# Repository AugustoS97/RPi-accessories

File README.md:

# RPi-accessories

Repositorio con diferentes PCBs de uso con Arduino y Rapsberry

## Contenido del repositorio

- [PCB para control PWM](/PWM-TRANSISTOR-PCB/) de elementos de tensión igual o superior a la de alimentación del microcontrolador. Compatible con Arduino, Raspberry, ESP, etc.

- [PCB de expansión para Rapsberry](/LED-RPi-PCB/). Permite alimentar RPi desde fuente externa, conectar un elementos para control PWM (ventilador por ejemplo), LEDs de estado, fusible de protección y pines de expansión para alimentación.

## Como ordenar las PCB

- Cada subproyecto dispone de una carpeta GERBER para ser subida a JLCPCB o PCBWAY y poder pedir las placas. Puedes adquirirse individualmente y soldadas contactando conmigo vía email: augustosamuelhdezmartin@gmail.com
- Existe una carpeta con GERBER para el panelizado de las PCB para ahorrar costes en JLCPCB.

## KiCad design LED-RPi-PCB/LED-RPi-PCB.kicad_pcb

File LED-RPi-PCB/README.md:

# PWM-RPi-PCB

Módulo de expansión para Rapsberry Pi. Permite alimentar RPi desde una fuente externa superior a 5V, incorpora un módulo para control PWM de una salida, LEDs indicadores de Estado y de Alimentación, Fusible de Protección, y pines de expansión para aumentar las conexiones de 3.3V y 5V. Diseñado para ser utilizado en el [NAS expuesto aquí](https://github.com/AugustoS97/Raspberry-Pi-NAS).

## Características

- Permite alimentar RPi desde una fuente externa superior a 5V con módulos LM2596 y MP2307
- Incorpora un módulo para control PWM de una salida de hasta 625mW
- LEDs indicadores de Estado y de Alimentación
- Fusible de Protección 5x20
- Pines de expansión para aumentar las conexiones de 3.3V y 5V
- Cuenta con Jumper (JP2) para desactivar o activar los LEDs indicadores
- Incorpora un Jumper/Pines (JP1) para conectar un interruptor de encendido y apagado del módulo mediante conectores Dupont
- Dimensiones 58,7mm x 43,9mm
- GERBER disponibles para solicitar las PCB. Si desea comprarlas ensambladas por unidades, puedes contactarme a augustosamuelhdezmartin@gmail.com

## Características de la salida PWM 

- Corriente máxima: 600mA
- Potencia máxima: 625mW
- Pensado para controlar motores desde Raspberry y Arduino (3,3V y 5V de señal de control). Puede modificarse R1 y R2 para ser utilizado con otras tensiones de control.

## Lista de materiales (BOM)

- Transistor 2N2222A SOT-23
- Resistencia 1206 1K 0.25W x2 unidades
- Resistencia 1206 10K 0.25W
- Resistencia 1206 220Ohm 
- Módulo DC/DC MP2307 o LM2596
- Diodo 1N4007 SOD-123F
- PinHeader 2.54mm 9 pines x2 unidades
- Portafuisble 5x20
- Jumpers x2 unidades
- LED 5mm x2 unidades (rojo y verde)
- PinHeader 2.54mm 2 pines x3 unidades
- Conector DC-Jack

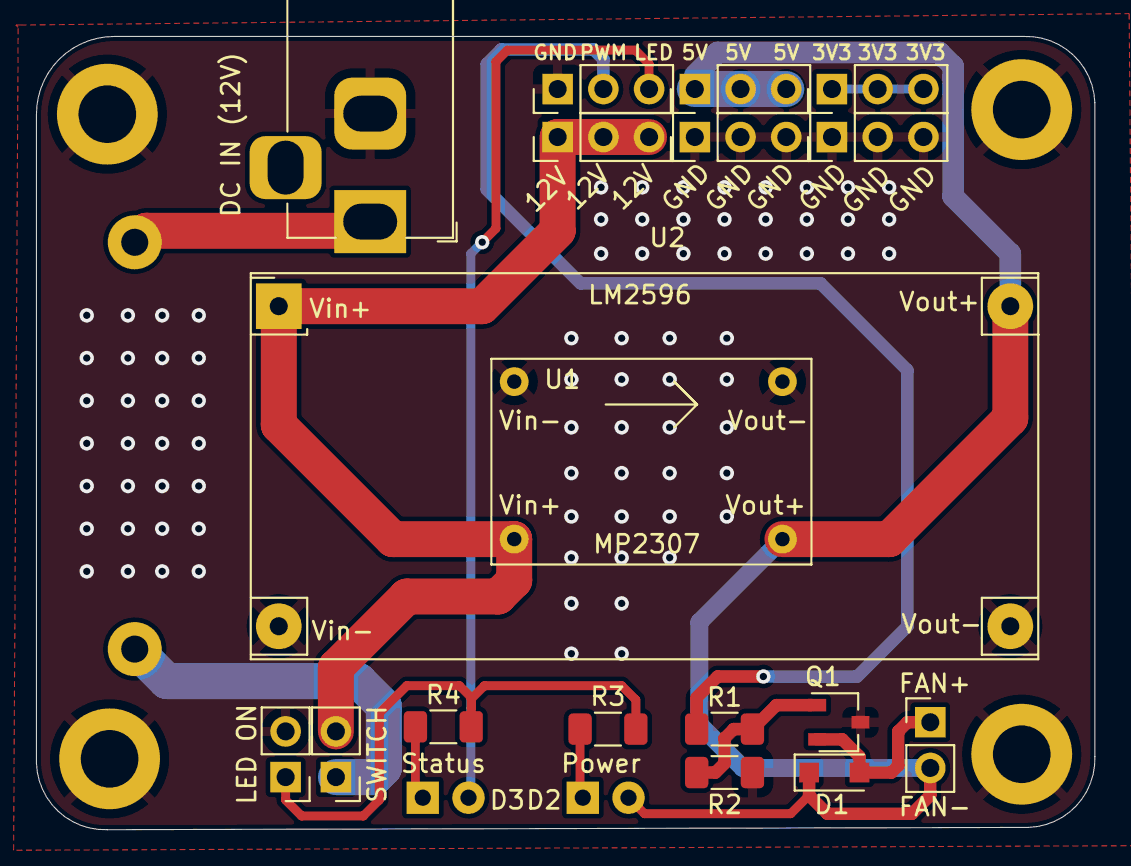
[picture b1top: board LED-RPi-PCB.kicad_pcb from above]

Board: 2 copper layers, 58.8 x 44.1 mm, 25 parts (0 on the bottom side), 13 nets.

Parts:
D1: 1N4007; D_SOD-123F
D2: RED; LED_D3.0mm_Horizontal_O1.27mm_Z2.0mm
D3: YELLOW; LED_D3.0mm_Horizontal_O1.27mm_Z2.0mm
F1: 1,5A; Fuseholder_Cylinder-5x20mm_Stelvio-Kontek_PTF78_Horizontal_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
H1, H2, H3, H4: MountingHole_Pad; MountingHole_3.2mm_M3_DIN965_Pad
J1: FAN_CON; PinHeader_1x02_P2.54mm_Vertical
J2: RPi_IN; PinHeader_1x03_P2.54mm_Vertical
J3, J8: GND_CON; PinHeader_1x03_P2.54mm_Vertical
J4: 12V_CON; PinHeader_1x03_P2.54mm_Vertical
J5: 5V_CON; PinHeader_1x03_P2.54mm_Vertical
J6: 3V3_CON; PinHeader_1x03_P2.54mm_Vertical
J7: Jack-DC; BarrelJack_Horizontal
JP1: Jumper & Switch; PinHeader_1x02_P2.54mm_Vertical
JP2: LED_ON; PinHeader_1x02_P2.54mm_Vertical
Q1: 2N2222A; SOT-23W
R1, R3: 1k; R_1206_3216Metric_Pad1.30x1.75mm_HandSolder
R2: 10k; R_1206_3216Metric_Pad1.30x1.75mm_HandSolder
R4: 220; R_1206_3216Metric_Pad1.30x1.75mm_HandSolder
U1: MP2307
U2: DCDC_StepDown_LM2596

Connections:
+3V3: J6.1, J6.2, J6.3
+5V: D1.1, D2.2, J1.2, J5.1, J5.2, J5.3, U1.3, U2.4
+12V: J4.1, J4.2, J4.3, JP1.2, U1.1, U2.1
/FAN_V-: D1.2, J1.1, Q1.2
GND: H1.1, H2.1, H3.1, H4.1, J2.1, J3.1, J3.2, J3.3, J7.2, J8.1, J8.2, J8.3, JP2.2, Q1.3, R2.2, U1.2, U1.4, U2.2, U2.3
unnamed: D2.1, R3.1
unnamed: D3.1, R4.1
unnamed: F1.1, JP1.1
unnamed: JP2.1, R3.2, R4.2
unnamed: Q1.1, R1.1, R2.1
PWM: J2.2, R1.2
StatusLED+: D3.2, J2.3
VDC: F1.2, J7.1

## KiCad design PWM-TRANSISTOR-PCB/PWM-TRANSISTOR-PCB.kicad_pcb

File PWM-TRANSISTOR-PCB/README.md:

# PWM-TRANSISTOR-PCB

Módulo para el control PWM de cualquier elemento que trabaje con tensión igual o superior a la de alimentación.

- Corriente máxima: 600mA
- Potencia máxima: 625mW
- Pensado para controlar motores desde Raspberry y Arduino (3,3V y 5V de señal de control). Puede modificarse R1 y R2 para ser utilizado con otras tensiones de control.
- GERBER disponibles para solicitar las PCB. Si desea comprarlas ensambladas por unidades, puedes contactarme a augustosamuelhdezmartin@gmail.com
- Dimensiones de la PCB 26,7mm x 23,9 mm.

## Lista de materiales (BOM)

- Transistor 2N2222A SOT-23
- Resistencia 1206 1K 0.25W
- Resistencia 1206 10K 0.25W
- Diodo 1N4007 SOD-123F
- PinHeader 2.54 2 pines x3 unidades
- Terminal Block 5.08mm

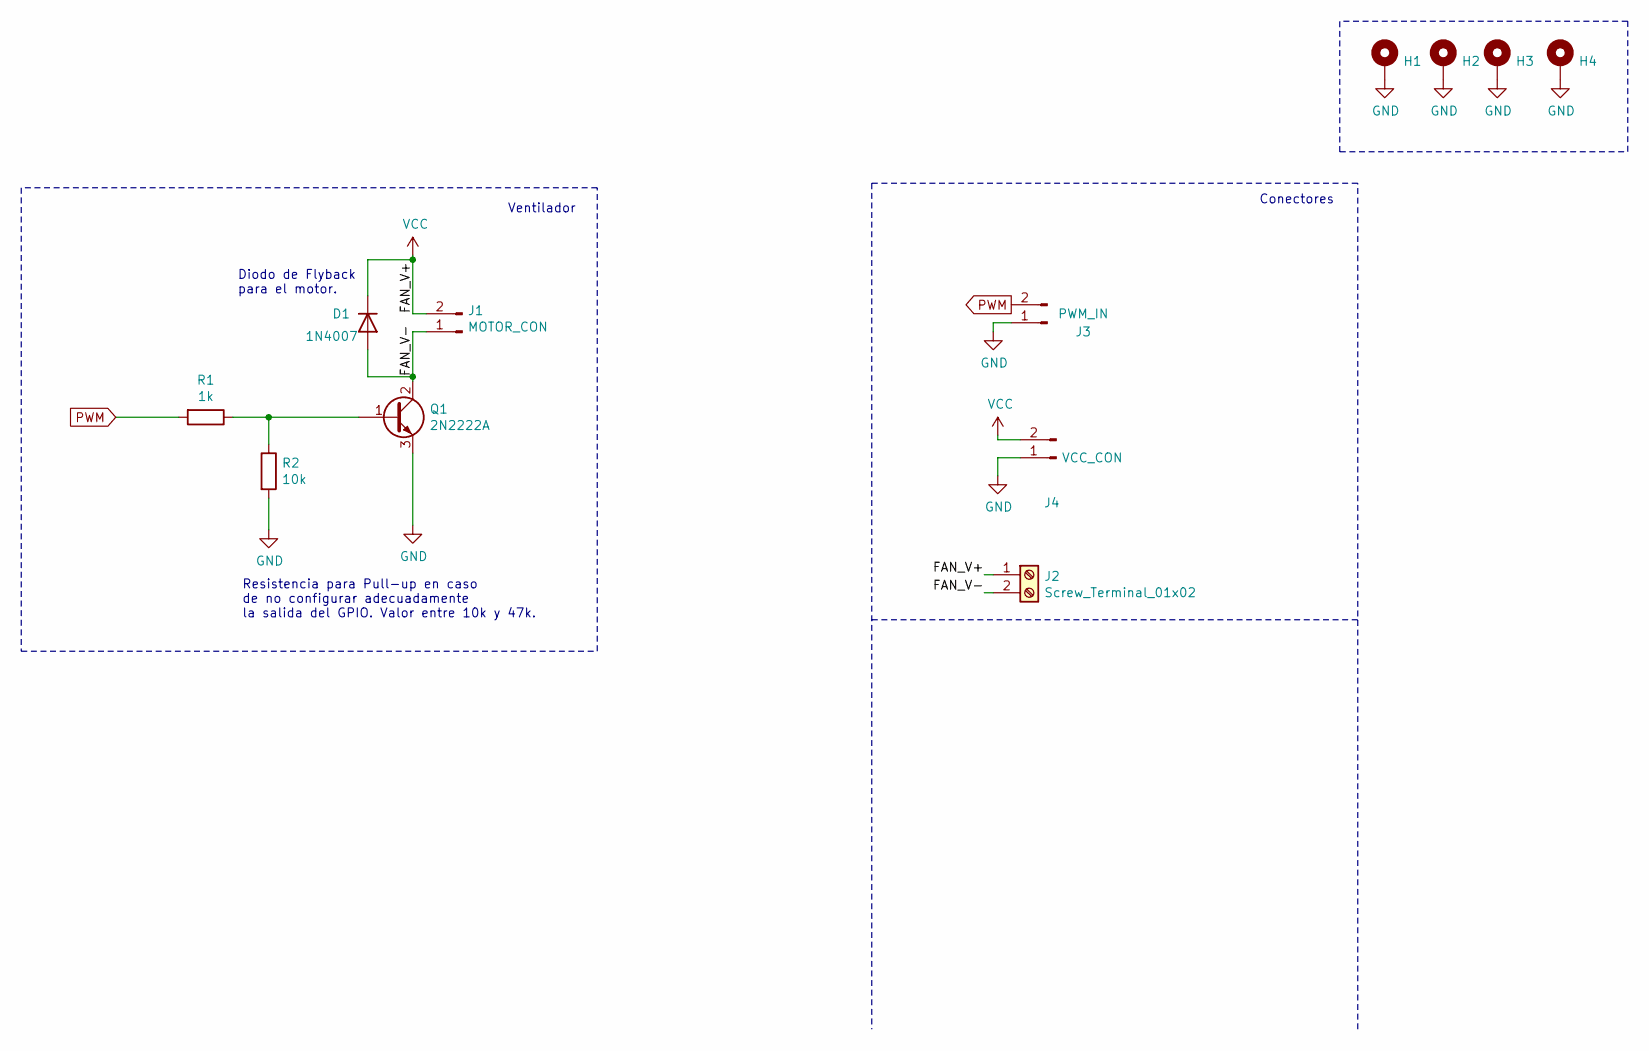
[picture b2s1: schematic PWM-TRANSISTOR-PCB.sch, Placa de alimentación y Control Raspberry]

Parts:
D1: 1N4007; D_SOD-123F
H1, H2, H3, H4: MountingHole_Pad; MountingHole_3.2mm_M3_DIN965_Pad
J1: MOTOR_CON; PinHeader_1x02_P2.54mm_Vertical
J2: Screw_Terminal_01x02; TerminalBlock_bornier-2_P5.08mm
J3: PWM_IN; PinHeader_1x02_P2.54mm_Vertical
J4: VCC_CON; PinHeader_1x02_P2.54mm_Vertical
Q1: 2N2222A; SOT-23_Handsoldering
R1: 1k; R_1206_3216Metric_Pad1.30x1.75mm_HandSolder
R2: 10k; R_1206_3216Metric_Pad1.30x1.75mm_HandSolder

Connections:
/FAN_V-: D1.2 (A), J1.1, J2.2, Q1.2 (C)
GND: H1.1, H2.1, H3.1, H4.1, J3.1, J4.1, Q1.3 (E), R2.2
unnamed: Q1.1 (B), R1.1, R2.1
PWM: J3.2, R1.2
VCC: D1.1 (K), J1.2, J2.1, J4.2

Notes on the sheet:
Resistencia para Pull-up en caso de no configurar adecuadamente la salida del GPIO. Valor entre 10k y 47k.
Diodo de Flyback para el motor.
Conectores
Ventilador

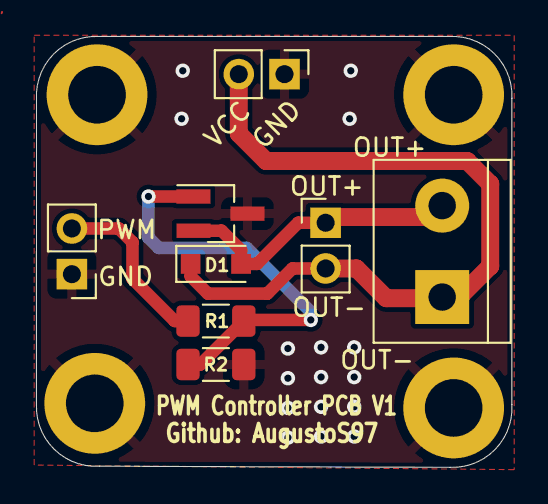
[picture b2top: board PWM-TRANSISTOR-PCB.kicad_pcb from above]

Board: 2 copper layers, 26.4 x 23.9 mm, 12 parts (0 on the bottom side), 5 nets.

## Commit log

2022-06-15 Creada la version V1.0 de la PCB para DCDC, ventilador y LEDs
2022-07-15 Creada PCB para controlar motores con PWM y Transistor. Añadidos logos DCD
2022-08-14 Añadidos las README así como GERBERS y RENDERs
2022-08-14 Eliminados ficheros extra
2022-11-14 Añadido STEP de PCB
2023-01-16 Añadido panelizado de PCB.
